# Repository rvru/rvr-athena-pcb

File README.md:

# RVR Athena PCB
**Contributor(s):** Jennifer Hellar 

**Contact(s):** jennifer.hellar@rice.edu

### Revisions
#### Rev. 0.1 (r0p1)
An initial (un-manufactured) design featuring a simplified version of the HiFive
reference design without the WiFi module and a new LiPo battery charger and
connector to enable IoT prototyping.

### Reference Designs
- SiFive HiFive Rev. B
- Sparkfun RED-V RedBoard
- Adafruit Feather M0 Bluefruit LE

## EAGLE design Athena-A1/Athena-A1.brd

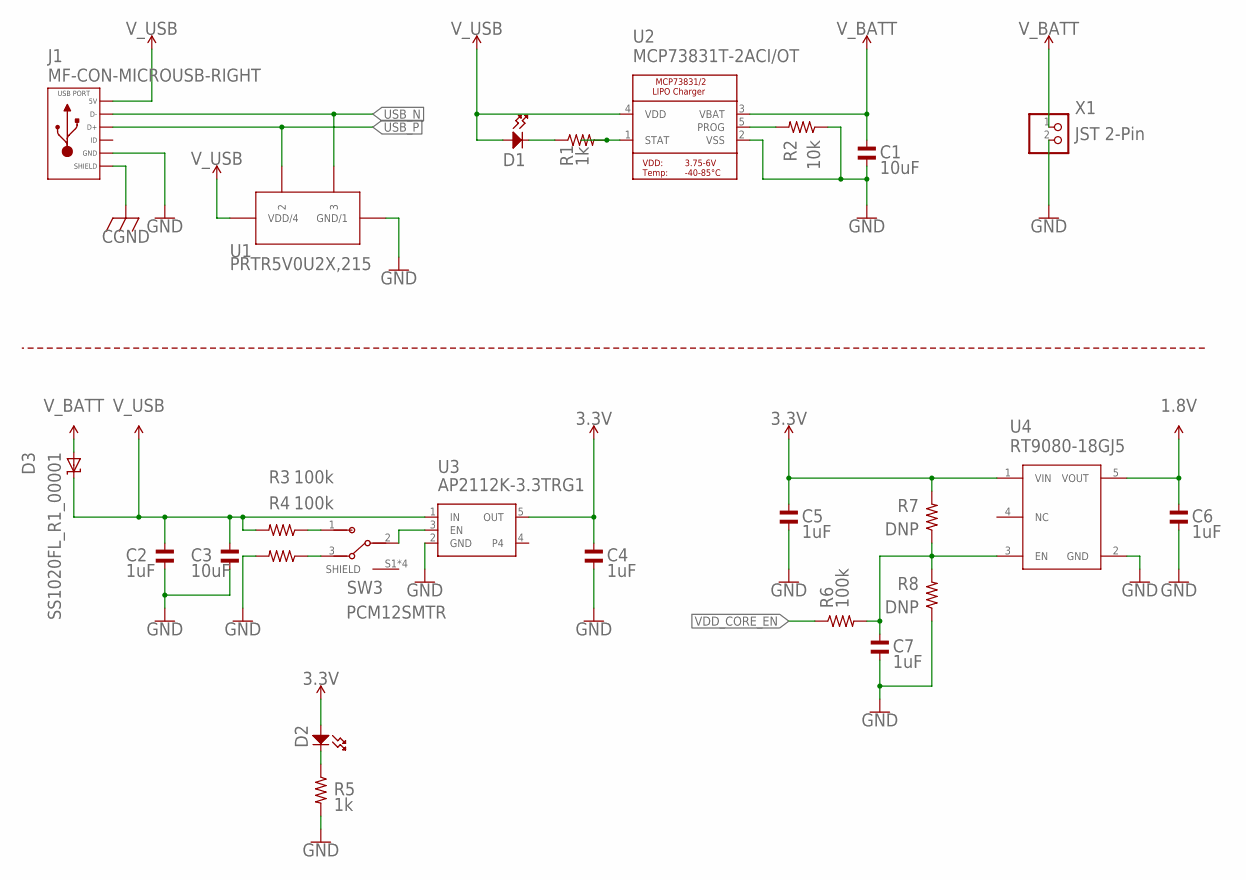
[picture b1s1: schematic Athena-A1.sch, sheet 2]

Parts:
C1, C3: 10uF; C0402; MPN CL05A106MP8NUB8
C2, C4, C5, C6, C7: 1uF; C0402
D1: MF-LED-0805-RED; LED0603
D2: MF-LED-0603-GREEN; LED0603
D3: SS1020FL_R1_00001; SOD-123
J1: MF-CON-MICROUSB-RIGHT; MICROUSB-RIGHT
R1, R5: 1k; R0402
R2: 10k; R0402
R3, R4, R6: 100k; R0402
R7, R8: DNP; R0402
SW3: PCM12SMTR; SW_PCM12SMTR
U1: PRTR5V0U2X,215; SOT143B_PRTR5V0U2X,215_NEX
U2: MCP73831T-2ACI/OT; SOT23-5
U3: AP2112K-3.3TRG1; SOT23-5
U4: RT9080-18GJ5; TSOT23-5_ONS
X1: JST 2-Pin; JSTPH2

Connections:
1.8V: C6.P$1, U4.5 (VOUT); also elsewhere on the board
3.3V: C4.P$1, C5.P$1, D2.ANODE, R7.P$2, U3.5 (OUT), U4.1 (VIN); also elsewhere on the board
CGND: J1.S1 (SLD), J1.S2 (SLD), J1.S3 (SLD), J1.S4 (SLD), J1.S5 (SLD), J1.S6 (SLD); also elsewhere on the board
GND: C1.P$2, C2.P$2, C3.P$2, C4.P$2, C5.P$2, C6.P$2, C7.P$2, J1.5 (GND), R2.P$1, R4.P$2, R5.P$2, R8.P$1, U1.1 (GND/1), U2.2 (VSS), U3.2 (GND), U4.2 (GND), X1.2; also elsewhere on the board
unnamed: R3.P$1, SW3.1
unnamed: D2.CATHODE, R5.P$1
unnamed: D1.CATHODE, R1.P$1
unnamed: C7.P$1, R6.P$2, R7.P$1, R8.P$2, U4.3 (EN)
unnamed: R2.P$2, U2.5 (PROG)
unnamed: R1.P$2, U2.1 (STAT)
unnamed: SW3.2, U3.3 (EN)
unnamed: R4.P$1, SW3.3
USB_N: J1.2 (D-), U1.3; also elsewhere on the board
USB_P: J1.3 (D+), U1.2; also elsewhere on the board
VDD_CORE_EN: R6.P$1; also elsewhere on the board
V_BATT: C1.P$1, D3.A, U2.3 (VBAT), X1.1
V_USB: C2.P$1, C3.P$1, D1.ANODE, D3.C, J1.1 (5V), R3.P$2, U1.4 (VDD/4), U2.4 (VDD), U3.1 (IN); also elsewhere on the board

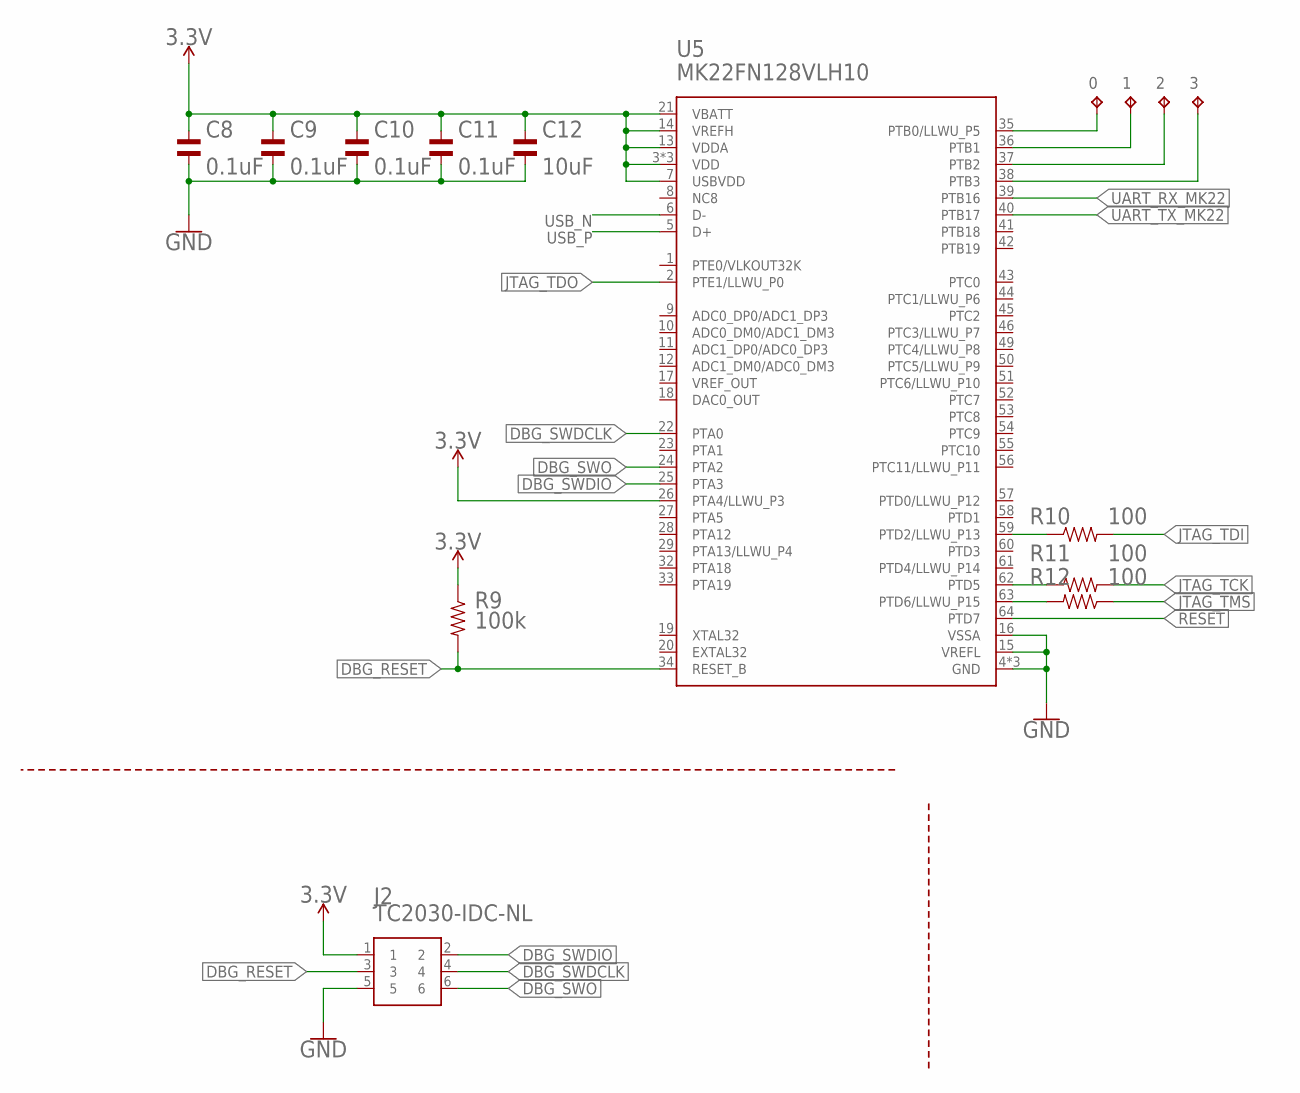
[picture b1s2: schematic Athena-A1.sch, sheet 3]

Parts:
0, 1, 2, 3: TPB0,65; TP_B0,65
C8, C9, C10, C11: 0.1uF; C0402
C12: 10uF; C0402; MPN CL05A106MP8NUB8
J2: TC2030-IDC-NL; TAG_TC2030-IDC-NL
R9: 100k; R0402
R10, R11, R12: 100; R0402
U5: MK22FN128VLH10; IC_USB_JTAG_LQFP-64

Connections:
3.3V: C8.P$1, C9.P$1, C10.P$1, C11.P$1, C12.P$1, J2.1, R9.P$1, U5.3 (VDD), U5.7 (USBVDD), U5.13 (VDDA), U5.14 (VREFH), U5.21 (VBATT), U5.26 (PTA4/LLWU_P3), U5.30 (VDD), U5.48 (VDD); also elsewhere on the board
DBG_RESET: J2.3, R9.P$2, U5.34 (RESET_B)
DBG_SWDCLK: J2.4, U5.22 (PTA0)
DBG_SWDIO: J2.2, U5.25 (PTA3)
DBG_SWO: J2.6, U5.24 (PTA2)
GND: C8.P$2, C9.P$2, C10.P$2, C11.P$2, C12.P$2, J2.5, U5.4 (GND), U5.15 (VREFL), U5.16 (VSSA), U5.31 (GND), U5.47 (GND); also elsewhere on the board
JTAG_TCK: R11.P$2; also elsewhere on the board
JTAG_TDI: R10.P$2; also elsewhere on the board
JTAG_TDO: U5.2 (PTE1/LLWU_P0); also elsewhere on the board
JTAG_TMS: R12.P$1; also elsewhere on the board
unnamed: R12.P$2, U5.63 (PTD6/LLWU_P15)
unnamed: R11.P$1, U5.62 (PTD5)
unnamed: R10.P$1, U5.59 (PTD2/LLWU_P13)
unnamed: 0.TP, U5.35 (PTB0/LLWU_P5)
unnamed: 1.TP, U5.36 (PTB1)
unnamed: 2.TP, U5.37 (PTB2)
unnamed: 3.TP, U5.38 (PTB3)
RESET: U5.64 (PTD7); also elsewhere on the board
UART_RX_MK22: U5.39 (PTB16); also elsewhere on the board
UART_TX_MK22: U5.40 (PTB17); also elsewhere on the board
USB_N: U5.6 (D-); also elsewhere on the board
USB_P: U5.5 (D+); also elsewhere on the board

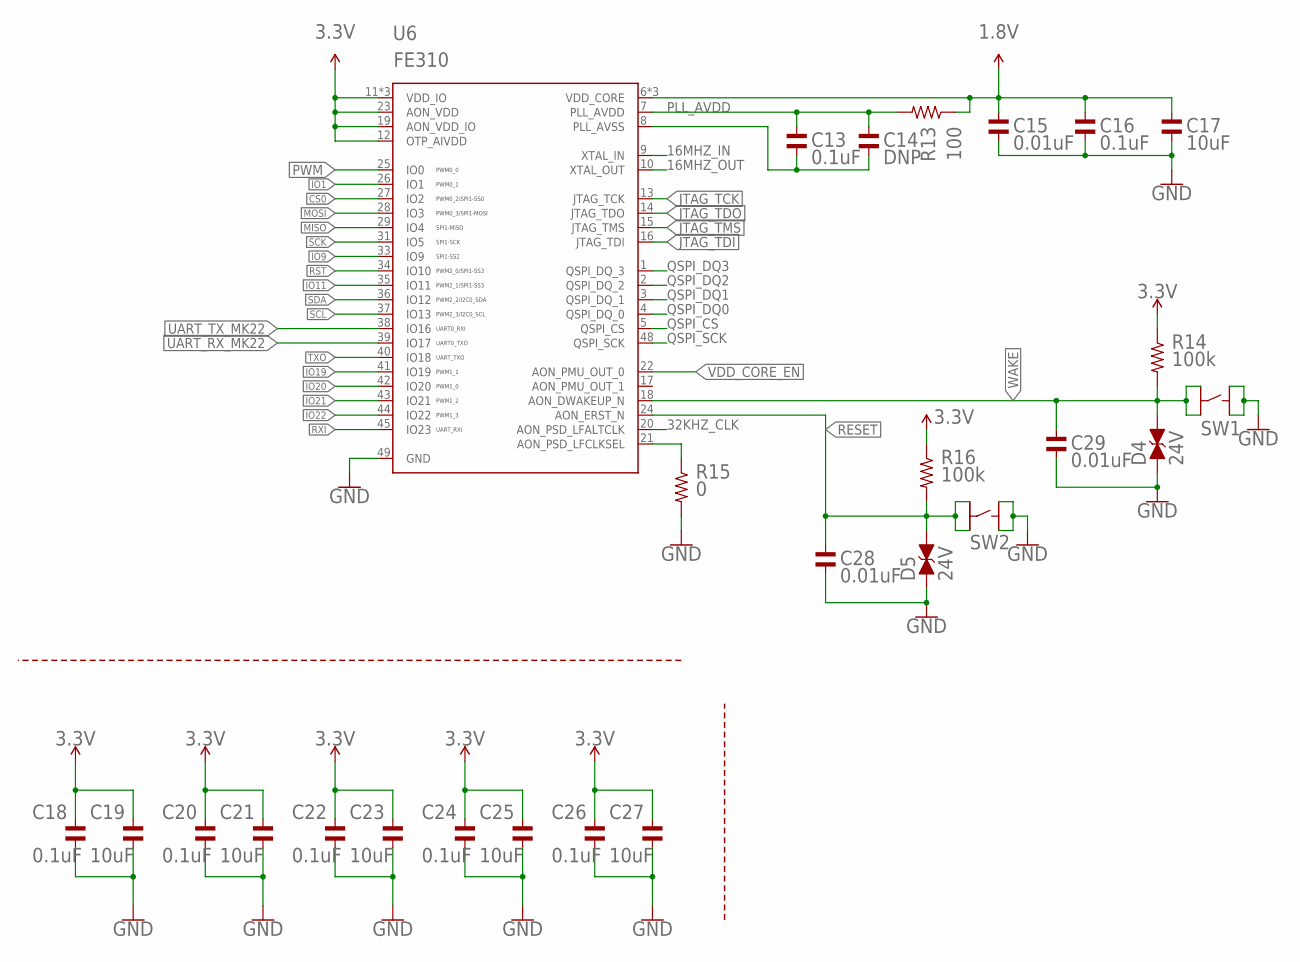
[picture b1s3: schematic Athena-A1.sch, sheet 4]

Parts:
C13, C16, C18, C20, C22, C24, C26: 0.1uF; C0402
C14: DNP; C0402
C15, C28, C29: 0.01uF; C0402
C17, C19, C21, C23, C25, C27: 10uF; C0402; MPN CL05A106MP8NUB8
D4, D5: 24V; TVS0603
R13: 100; R0402
R14, R16: 100k; R0402
R15: 0; R0402
SW1, SW2: MF-SW-TACT-6MM; TACT4.2MM
U6: FE310; MCU_QFN-48-.4MMPITCH

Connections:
1.8V: C15.P$1, C16.P$1, C17.P$1, R13.P$1, U6.6 (VDD_CORE), U6.30 (VDD_CORE), U6.46 (VDD_CORE); also elsewhere on the board
3.3V: C18.P$1, C19.P$1, C20.P$1, C21.P$1, C22.P$1, C23.P$1, C24.P$1, C25.P$1, C26.P$1, C27.P$1, R14.P$1, R16.P$1, U6.11 (VDD_IO), U6.12 (OTP_AIVDD), U6.19 (AON_VDD_IO), U6.23 (AON_VDD), U6.32 (VDD_IO), U6.47 (VDD_IO); also elsewhere on the board
16MHZ_IN: U6.9 (XTAL_IN); also elsewhere on the board
16MHZ_OUT: U6.10 (XTAL_OUT); also elsewhere on the board
32KHZ_CLK: U6.20 (AON_PSD_LFALTCLK); also elsewhere on the board
CS0: U6.27 (IO2); also elsewhere on the board
GND: C15.P$2, C16.P$2, C17.P$2, C18.P$2, C19.P$2, C20.P$2, C21.P$2, C22.P$2, C23.P$2, C24.P$2, C25.P$2, C26.P$2, C27.P$2, C28.P$2, C29.P$2, D4.1 (A), D5.1 (A), R15.P$2, SW1.P$1, SW1.P$2, SW2.P$1, SW2.P$2, U6.49 (GND); also elsewhere on the board
IO1: U6.26 (IO1); also elsewhere on the board
IO9: U6.33 (IO9); also elsewhere on the board
IO11: U6.35 (IO11); also elsewhere on the board
IO19: U6.41 (IO19); also elsewhere on the board
IO20: U6.42 (IO20); also elsewhere on the board
IO21: U6.43 (IO21); also elsewhere on the board
IO22: U6.44 (IO22); also elsewhere on the board
JTAG_TCK: U6.13 (JTAG_TCK); also elsewhere on the board
JTAG_TDI: U6.16 (JTAG_TDI); also elsewhere on the board
JTAG_TDO: U6.14 (JTAG_TDO); also elsewhere on the board
JTAG_TMS: U6.15 (JTAG_TMS); also elsewhere on the board
MISO: U6.29 (IO4); also elsewhere on the board
MOSI: U6.28 (IO3); also elsewhere on the board
unnamed: R15.P$1, U6.21 (AON_PSD_LFCLKSEL)
unnamed: C13.P$2, C14.P$2, U6.8 (PLL_AVSS)
PLL_AVDD: C13.P$1, C14.P$1, R13.P$2, U6.7 (PLL_AVDD)
PWM: U6.25 (IO0); also elsewhere on the board
QSPI_CS: U6.5 (QSPI_CS); also elsewhere on the board
QSPI_DQ0: U6.4 (QSPI_DQ_0); also elsewhere on the board
QSPI_DQ1: U6.3 (QSPI_DQ_1); also elsewhere on the board
QSPI_DQ2: U6.2 (QSPI_DQ_2); also elsewhere on the board
QSPI_DQ3: U6.1 (QSPI_DQ_3); also elsewhere on the board
QSPI_SCK: U6.48 (QSPI_SCK); also elsewhere on the board
RESET: C28.P$1, D5.2 (C), R16.P$2, SW2.P$3, SW2.P$4, U6.24 (AON_ERST_N); also elsewhere on the board
RST: U6.34 (IO10); also elsewhere on the board
RXI: U6.45 (IO23); also elsewhere on the board
SCK: U6.31 (IO5); also elsewhere on the board
SCL: U6.37 (IO13); also elsewhere on the board
SDA: U6.36 (IO12); also elsewhere on the board
TXO: U6.40 (IO18); also elsewhere on the board
UART_RX_MK22: U6.39 (IO17); also elsewhere on the board
UART_TX_MK22: U6.38 (IO16); also elsewhere on the board
VDD_CORE_EN: U6.22 (AON_PMU_OUT_0); also elsewhere on the board
WAKE: C29.P$1, D4.2 (C), R14.P$2, SW1.P$3, SW1.P$4, U6.18 (AON_DWAKEUP_N)

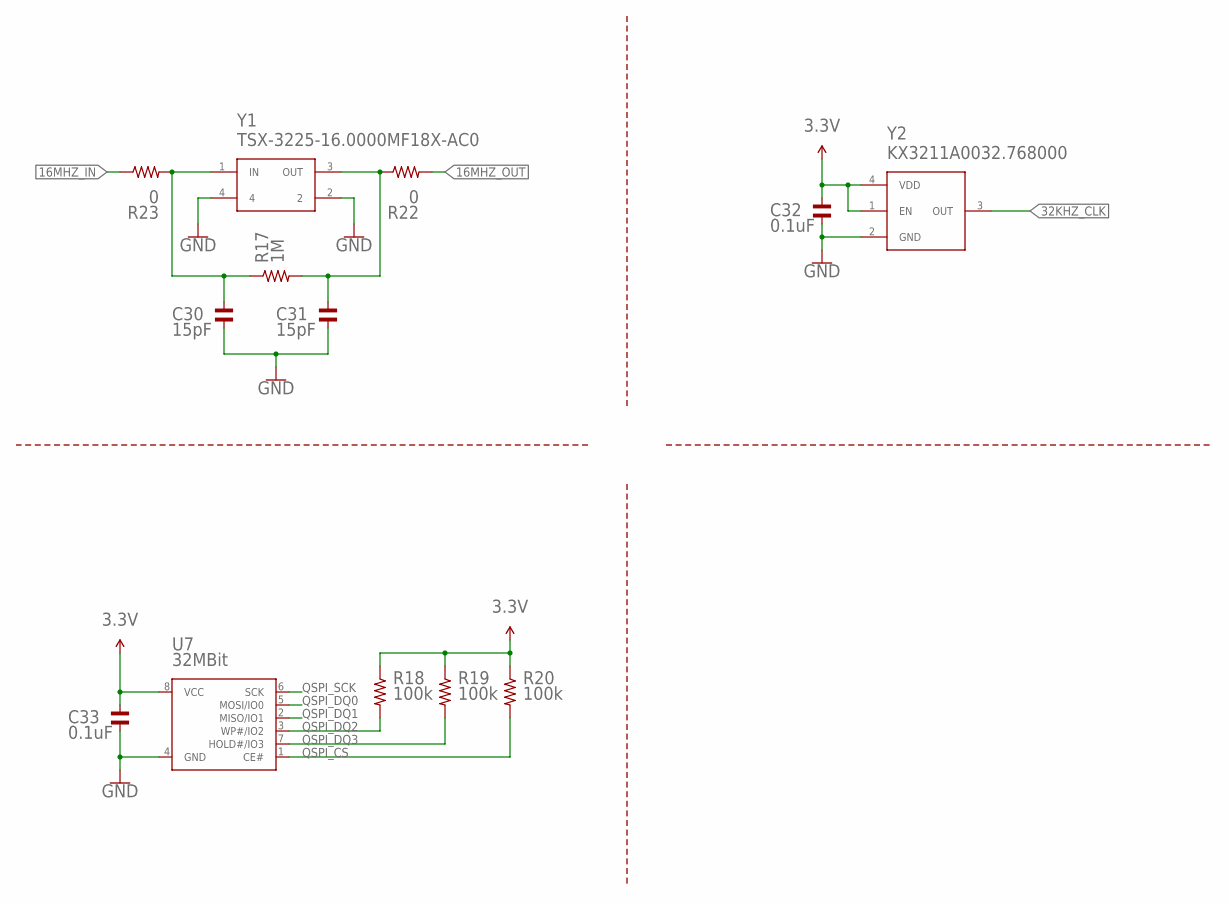
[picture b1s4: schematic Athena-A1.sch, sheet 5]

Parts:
C30, C31: 15pF; C0402; MPN CL05C150JB5NNNC
C32, C33: 0.1uF; C0402
R17: 1M; R0402
R18, R19, R20: 100k; R0402
R22, R23: 0; R0402
U7: 32MBit; IC-MEMORY_SO08
Y1: TSX-3225-16.0000MF18X-AC0; SMD-4
Y2: KX3211A0032.768000; SMD-4

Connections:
3.3V: C32.P$1, C33.P$1, R18.P$1, R19.P$1, R20.P$1, U7.8 (VCC), Y2.1 (EN), Y2.4 (VDD); also elsewhere on the board
16MHZ_IN: R23.P$1; also elsewhere on the board
16MHZ_OUT: R22.P$2; also elsewhere on the board
32KHZ_CLK: Y2.3 (OUT); also elsewhere on the board
GND: C30.P$2, C31.P$2, C32.P$2, C33.P$2, U7.4 (GND), Y1.2, Y1.4, Y2.2 (GND); also elsewhere on the board
unnamed: C30.P$1, R17.P$1, R23.P$2, Y1.1 (IN)
unnamed: C31.P$1, R17.P$2, R22.P$1, Y1.3 (OUT)
QSPI_CS: R20.P$2, U7.1 (CE#); also elsewhere on the board
QSPI_DQ0: U7.5 (MOSI/IO0); also elsewhere on the board
QSPI_DQ1: U7.2 (MISO/IO1); also elsewhere on the board
QSPI_DQ2: R18.P$2, U7.3 (WP#/IO2); also elsewhere on the board
QSPI_DQ3: R19.P$2, U7.7 (HOLD#/IO3); also elsewhere on the board
QSPI_SCK: U7.6 (SCK); also elsewhere on the board

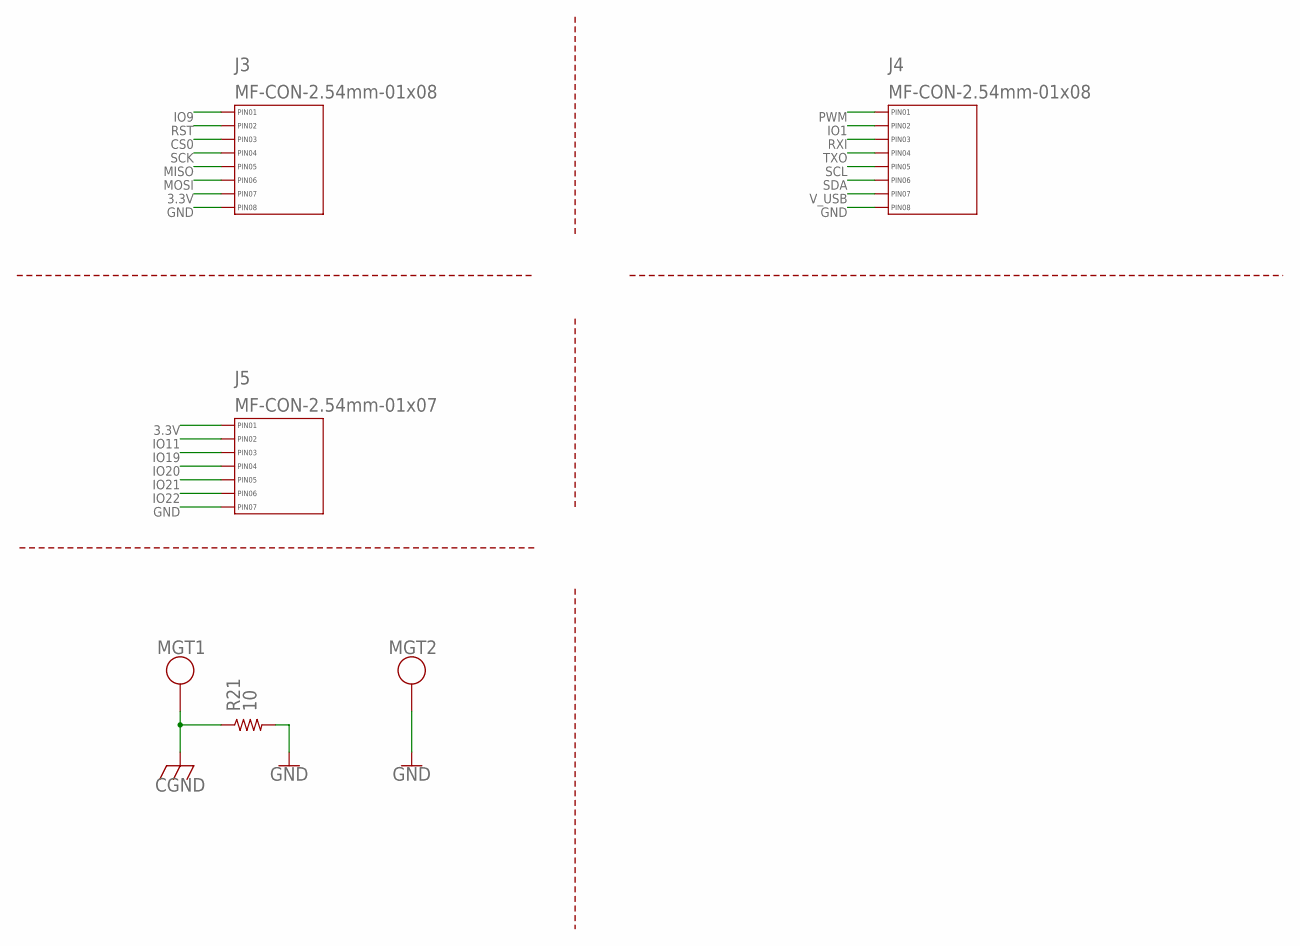
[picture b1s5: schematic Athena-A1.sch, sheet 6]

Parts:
J3, J4: MF-CON-2.54mm-01x08; PTH_2.54MM_01X08
J5: MF-CON-2.54mm-01x07; PTH_2.54MM_01X07
MGT1, MGT2: MOUNTING_HOLE
R21: 10; R0402

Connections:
3.3V: J3.P$7 (PIN7), J5.P$1 (PIN1); also elsewhere on the board
CGND: MGT1.P$1, R21.P$1; also elsewhere on the board
CS0: J3.P$3 (PIN3); also elsewhere on the board
GND: J3.P$8 (PIN8), J4.P$8 (PIN8), J5.P$7 (PIN7), MGT2.P$1, R21.P$2; also elsewhere on the board
IO1: J4.P$2 (PIN2); also elsewhere on the board
IO9: J3.P$1 (PIN1); also elsewhere on the board
IO11: J5.P$2 (PIN2); also elsewhere on the board
IO19: J5.P$3 (PIN3); also elsewhere on the board
IO20: J5.P$4 (PIN4); also elsewhere on the board
IO21: J5.P$5 (PIN5); also elsewhere on the board
IO22: J5.P$6 (PIN6); also elsewhere on the board
MISO: J3.P$5 (PIN5); also elsewhere on the board
MOSI: J3.P$6 (PIN6); also elsewhere on the board
PWM: J4.P$1 (PIN1); also elsewhere on the board
RST: J3.P$2 (PIN2); also elsewhere on the board
RXI: J4.P$3 (PIN3); also elsewhere on the board
SCK: J3.P$4 (PIN4); also elsewhere on the board
SCL: J4.P$5 (PIN5); also elsewhere on the board
SDA: J4.P$6 (PIN6); also elsewhere on the board
TXO: J4.P$4 (PIN4); also elsewhere on the board
V_USB: J4.P$7 (PIN7); also elsewhere on the board

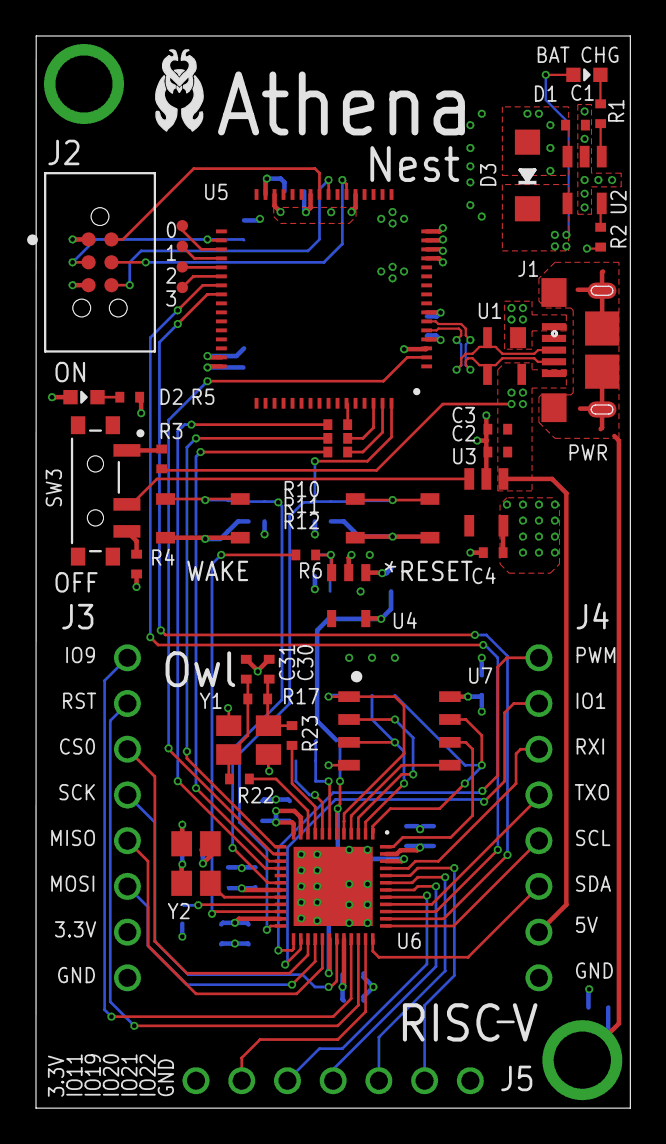
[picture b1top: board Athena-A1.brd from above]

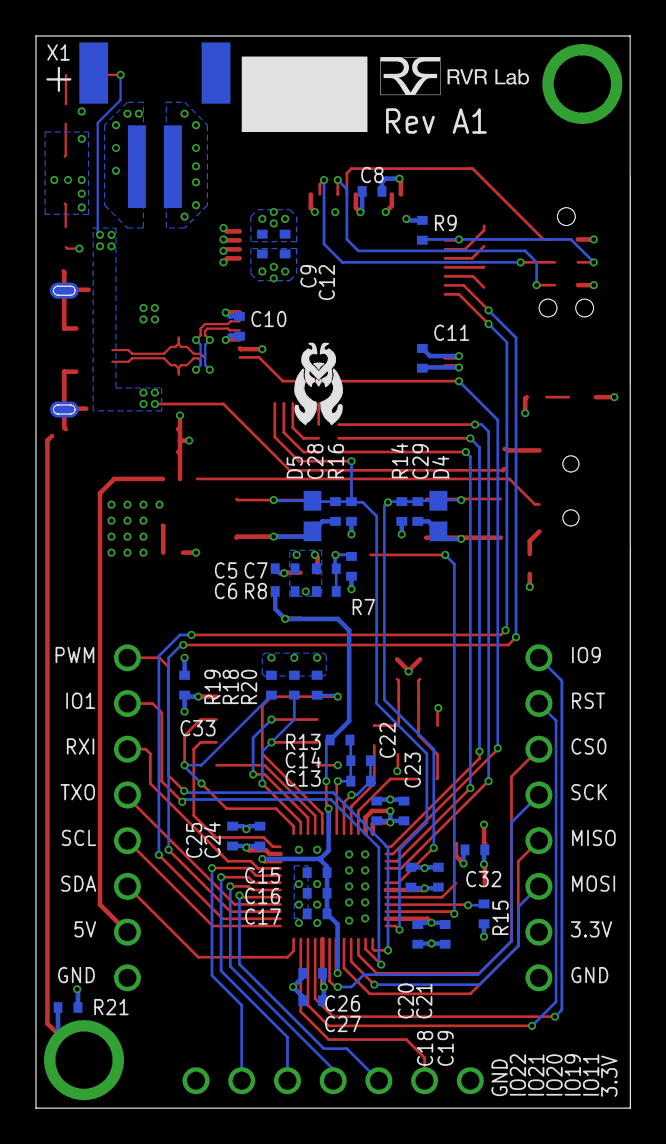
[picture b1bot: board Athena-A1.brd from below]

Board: 4 copper layers, 33.0 x 59.6 mm, 85 parts (41 on the bottom side), 67 nets.

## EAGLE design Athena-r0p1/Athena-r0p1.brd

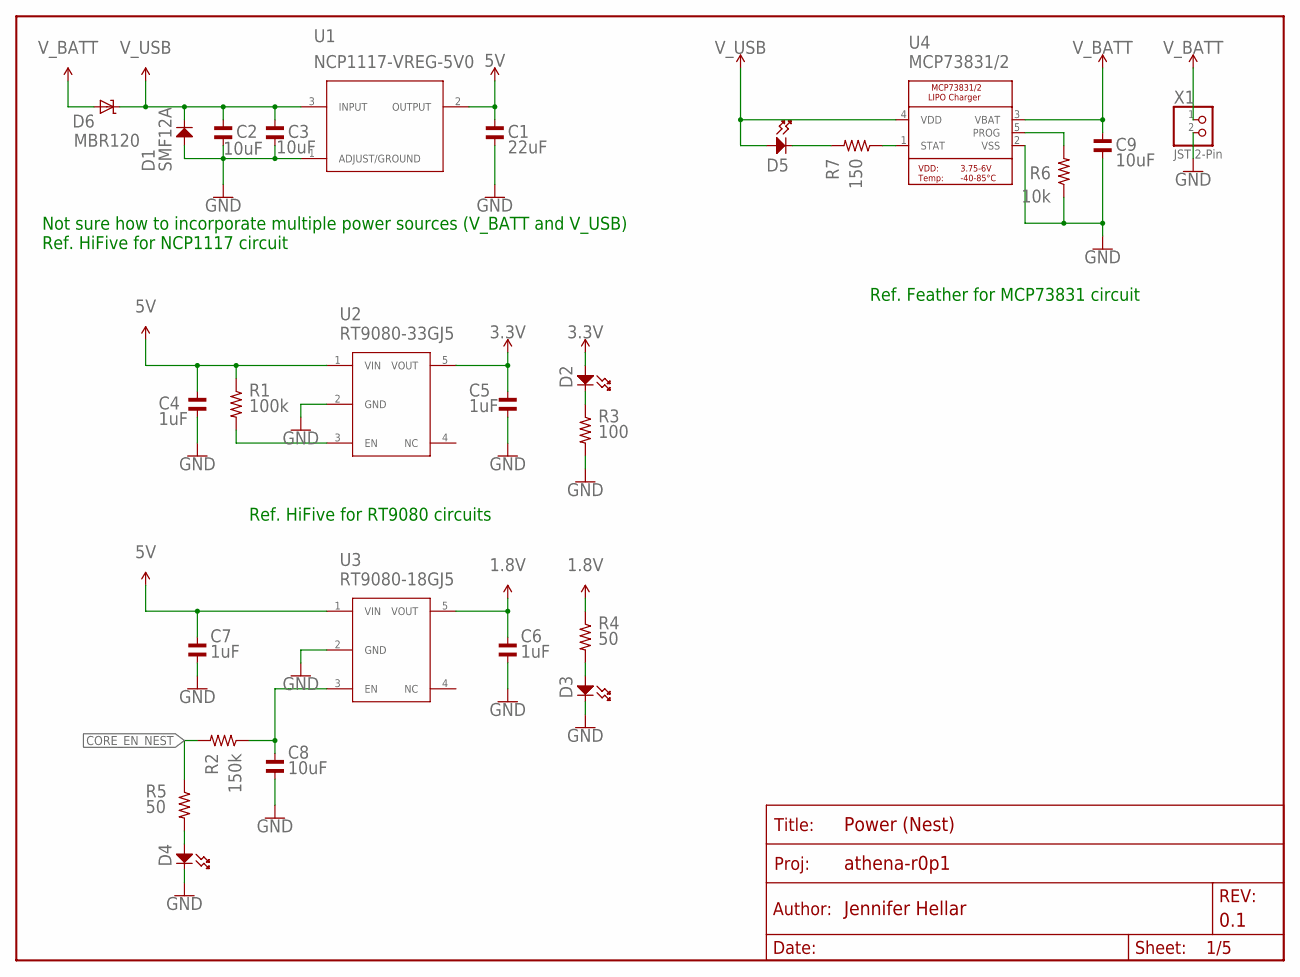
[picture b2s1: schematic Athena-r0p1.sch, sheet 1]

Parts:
C1: 22uF; C0603
C2, C3, C8, C9: 10uF; C0603
C4, C5, C6, C7: 1uF; C0603
D1: SMF12A; SMFSERIES_LTF
D2, D3, D4: MF-LED-0603-GREEN; LED0603
D5: MF-LED-0603-RED; LED0603
D6: MBR120; SOD-123
FRAME1: FRAME-LETTER; SPARKFUN-AESTHETICS_CREATIVE_COMMONS
R1: 100k; R0603
R2: 150k; R0603
R3: 100; R0603
R4, R5: 50; R0603
R6: 10k; R0603
R7: 150; R0603
U1: NCP1117-VREG-5V0; SOT223-3_ONS
U2: RT9080-33GJ5; TSOT23-5_ONS
U3: RT9080-18GJ5; TSOT23-5_ONS
U4: MCP73831/2; SOT23-5
X1: JST 2-Pin; JSTPH2

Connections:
1.8V: C6.P$1, R4.P$1, U3.5 (VOUT); also elsewhere on the board
3.3V: C5.P$1, D2.ANODE, U2.5 (VOUT); also elsewhere on the board
5V: C1.P$1, C4.P$1, C7.P$1, R1.P$1, U1.2 (OUTPUT), U2.1 (VIN), U3.1 (VIN); also elsewhere on the board
CORE_EN_NEST: R2.P$2, R5.P$1; also elsewhere on the board
GND: C1.P$2, C2.P$2, C3.P$2, C4.P$2, C5.P$2, C6.P$2, C7.P$2, C8.P$2, C9.P$2, D1.2 (ANODE), D3.CATHODE, D4.CATHODE, R3.P$2, R6.P$1, U1.1 (ADJUST/GROUND), U2.2 (GND), U3.2 (GND), U4.2 (VSS), X1.2; also elsewhere on the board
unnamed: D3.ANODE, R4.P$2
unnamed: D2.CATHODE, R3.P$1
unnamed: R1.P$2, U2.3 (EN)
unnamed: C8.P$1, R2.P$1, U3.3 (EN)
unnamed: D4.ANODE, R5.P$2
unnamed: R7.P$1, U4.1 (STAT)
unnamed: R6.P$2, U4.5 (PROG)
unnamed: D5.CATHODE, R7.P$2
V_BATT: C9.P$1, D6.A, U4.3 (VBAT), X1.1
V_USB: C2.P$1, C3.P$1, D1.1 (CATHODE), D5.ANODE, D6.C, U1.3 (INPUT), U4.4 (VDD); also elsewhere on the board

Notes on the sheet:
Not sure how to incorporate multiple power sources (V_BATT and V_USB) Ref. HiFive for NCP1117 circuit
Ref. HiFive for RT9080 circuits
Ref. Feather for MCP73831 circuit

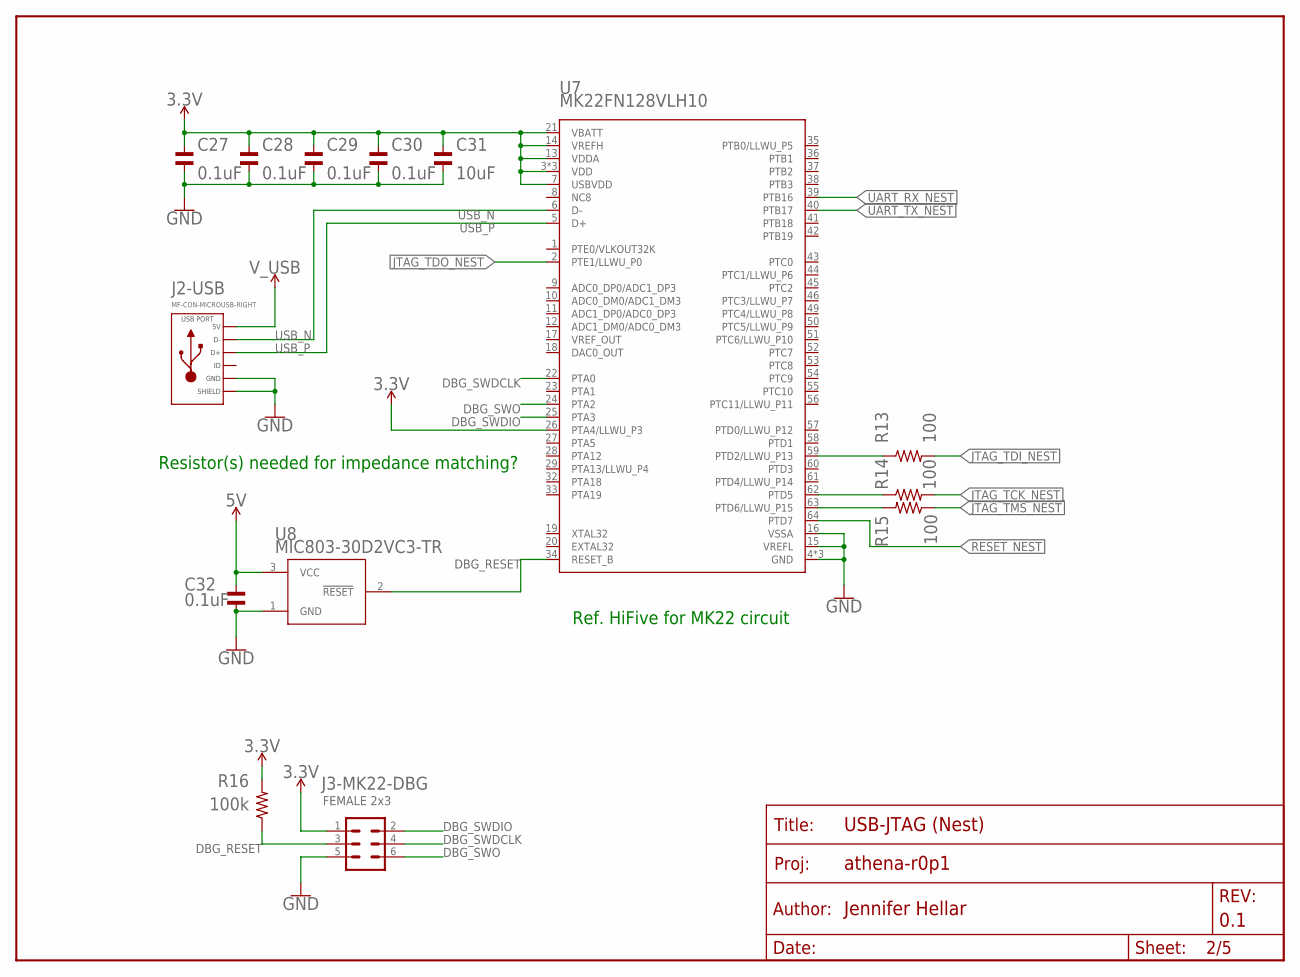
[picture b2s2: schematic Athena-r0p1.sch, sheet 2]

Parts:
C27, C28, C29, C30, C32: 0.1uF; C0603
C31: 10uF; C0603
FRAME3: FRAME-LETTER; SPARKFUN-AESTHETICS_CREATIVE_COMMONS
J2-USB: MF-CON-MICROUSB-RIGHT; MICROUSB-RIGHT
J3-MK22-DBG: FEMALE 2x3; 2X3
R13, R14, R15: 100; R0603
R16: 100k; R0603
U7: MK22FN128VLH10; IC_USB_JTAG_LQFP-64
U8: MIC803-30D2VC3-TR; SC-70_C3_MCH

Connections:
3.3V: C27.P$1, C28.P$1, C29.P$1, C30.P$1, C31.P$1, J3-MK22-DBG.1, R16.P$2, U7.3 (VDD), U7.7 (USBVDD), U7.13 (VDDA), U7.14 (VREFH), U7.21 (VBATT), U7.26 (PTA4/LLWU_P3), U7.30 (VDD), U7.48 (VDD); also elsewhere on the board
5V: C32.P$1, U8.3 (VCC); also elsewhere on the board
DBG_RESET: J3-MK22-DBG.3, R16.P$1, U7.34 (RESET_B), U8.2 (!RESET)
DBG_SWDCLK: J3-MK22-DBG.4, U7.22 (PTA0)
DBG_SWDIO: J3-MK22-DBG.2, U7.25 (PTA3)
DBG_SWO: J3-MK22-DBG.6, U7.24 (PTA2)
GND: C27.P$2, C28.P$2, C29.P$2, C30.P$2, C31.P$2, C32.P$2, J2-USB.5 (GND), J2-USB.S1 (SLD), J2-USB.S2 (SLD), J2-USB.S3 (SLD), J2-USB.S4 (SLD), J2-USB.S5 (SLD), J2-USB.S6 (SLD), J3-MK22-DBG.5, U7.4 (GND), U7.15 (VREFL), U7.16 (VSSA), U7.31 (GND), U7.47 (GND), U8.1 (GND); also elsewhere on the board
JTAG_TCK_NEST: R14.P$2; also elsewhere on the board
JTAG_TDI_NEST: R13.P$2; also elsewhere on the board
JTAG_TDO_NEST: U7.2 (PTE1/LLWU_P0); also elsewhere on the board
JTAG_TMS_NEST: R15.P$1; also elsewhere on the board
unnamed: R13.P$1, U7.59 (PTD2/LLWU_P13)
unnamed: R14.P$1, U7.62 (PTD5)
unnamed: R15.P$2, U7.63 (PTD6/LLWU_P15)
RESET_NEST: U7.64 (PTD7); also elsewhere on the board
UART_RX_NEST: U7.39 (PTB16); also elsewhere on the board
UART_TX_NEST: U7.40 (PTB17); also elsewhere on the board
USB_N: J2-USB.2 (D-), U7.6 (D-)
USB_P: J2-USB.3 (D+), U7.5 (D+)
V_USB: J2-USB.1 (5V); also elsewhere on the board

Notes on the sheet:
Resistor(s) needed for impedance matching?
Ref. HiFive for MK22 circuit

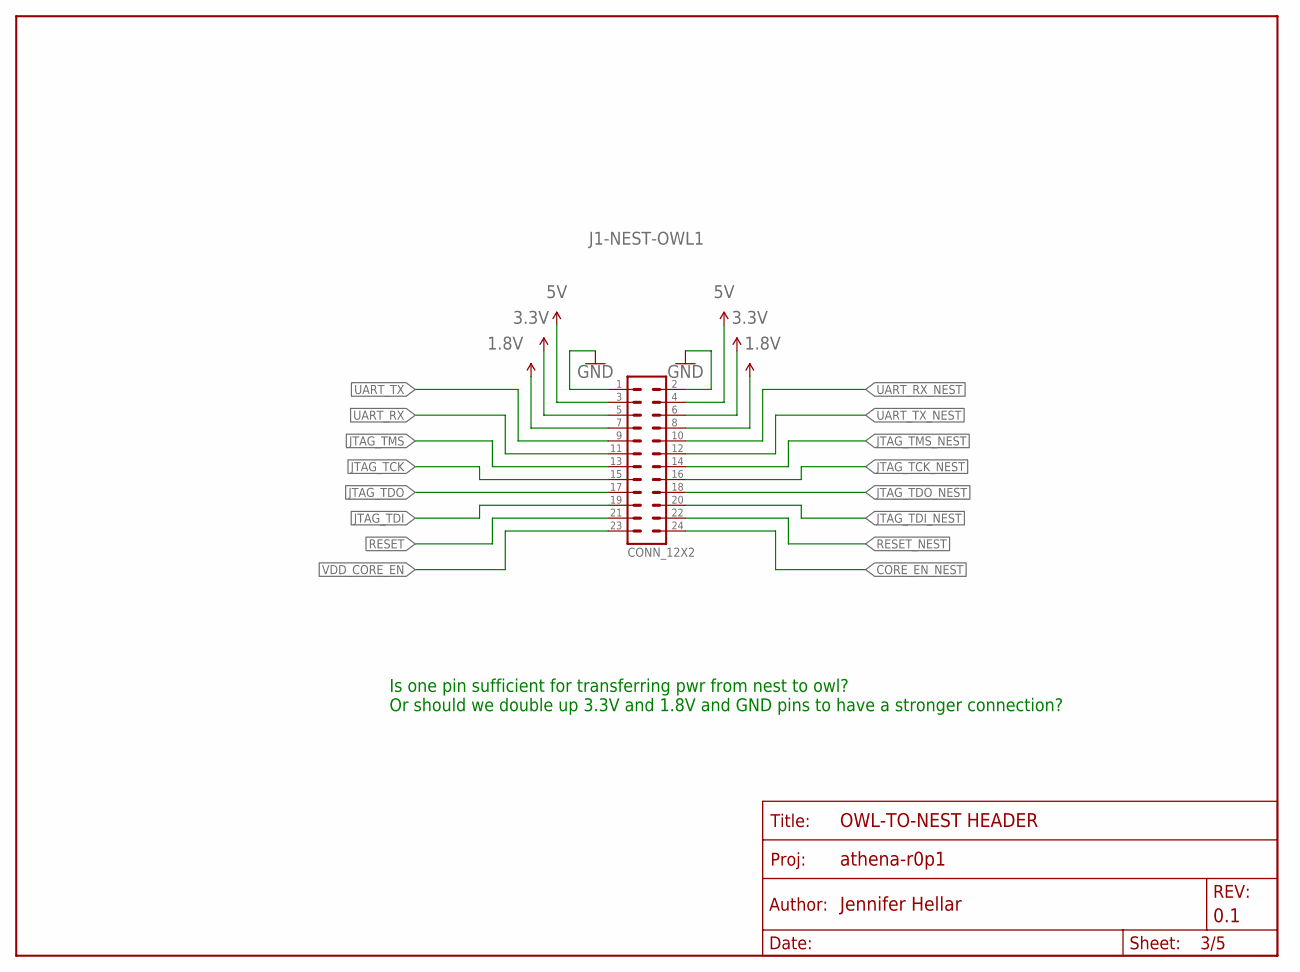
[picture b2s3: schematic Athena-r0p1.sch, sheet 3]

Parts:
FRAME5: FRAME-LETTER; SPARKFUN-AESTHETICS_CREATIVE_COMMONS
J1-NEST-OWL1: CONN_12X2; 2X12

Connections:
1.8V: J1-NEST-OWL1.7, J1-NEST-OWL1.8; also elsewhere on the board
3.3V: J1-NEST-OWL1.5, J1-NEST-OWL1.6; also elsewhere on the board
5V: J1-NEST-OWL1.3, J1-NEST-OWL1.4; also elsewhere on the board
CORE_EN_NEST: J1-NEST-OWL1.24; also elsewhere on the board
GND: J1-NEST-OWL1.1, J1-NEST-OWL1.2; also elsewhere on the board
JTAG_TCK: J1-NEST-OWL1.15; also elsewhere on the board
JTAG_TCK_NEST: J1-NEST-OWL1.16; also elsewhere on the board
JTAG_TDI: J1-NEST-OWL1.19; also elsewhere on the board
JTAG_TDI_NEST: J1-NEST-OWL1.20; also elsewhere on the board
JTAG_TDO: J1-NEST-OWL1.17; also elsewhere on the board
JTAG_TDO_NEST: J1-NEST-OWL1.18; also elsewhere on the board
JTAG_TMS: J1-NEST-OWL1.13; also elsewhere on the board
JTAG_TMS_NEST: J1-NEST-OWL1.14; also elsewhere on the board
RESET: J1-NEST-OWL1.21; also elsewhere on the board
RESET_NEST: J1-NEST-OWL1.22; also elsewhere on the board
UART_RX: J1-NEST-OWL1.11; also elsewhere on the board
UART_RX_NEST: J1-NEST-OWL1.10; also elsewhere on the board
UART_TX: J1-NEST-OWL1.9; also elsewhere on the board
UART_TX_NEST: J1-NEST-OWL1.12; also elsewhere on the board
VDD_CORE_EN: J1-NEST-OWL1.23; also elsewhere on the board

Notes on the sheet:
Is one pin sufficient for transferring pwr from nest to owl? Or should we double up 3.3V and 1.8V and GND pins to have a stronger connection?

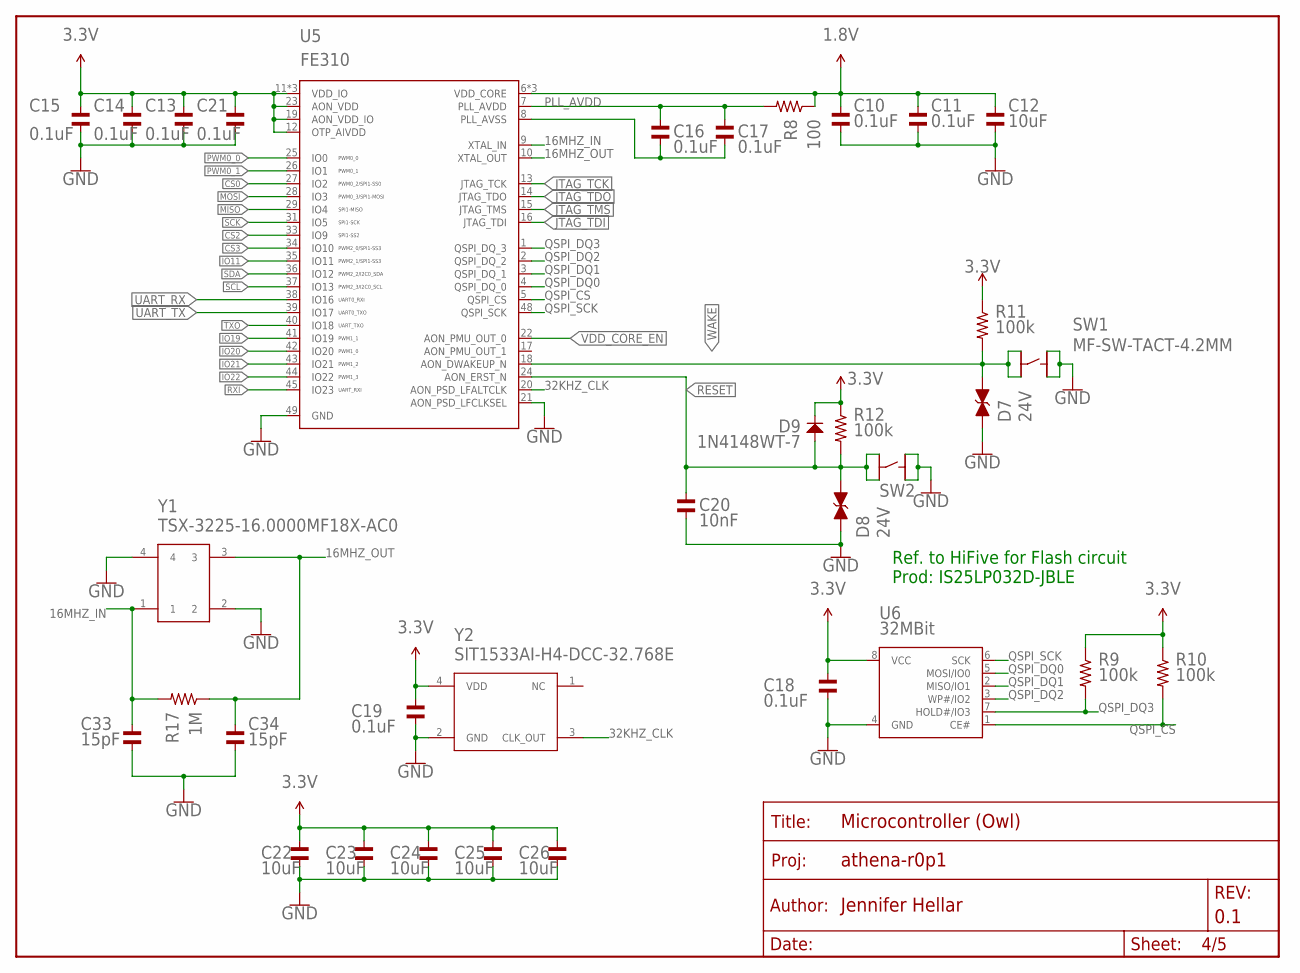
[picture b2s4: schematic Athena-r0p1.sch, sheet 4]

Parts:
C10, C11, C13, C14, C15, C16, C17, C18, C19, C21: 0.1uF; C0603
C12, C22, C23, C24, C25, C26: 10uF; C0603
C20: 10nF; C0603
C33, C34: 15pF; C0603
D7, D8: 24V; SPARKFUN-DISCRETESEMI_0603
D9: 1N4148WT-7; SOD-523
FRAME2: FRAME-LETTER; SPARKFUN-AESTHETICS_CREATIVE_COMMONS
R8: 100; R0603
R9, R10, R11, R12: 100k; R0603
R17: 1M; R0603
SW1, SW2: MF-SW-TACT-4.2MM; TACT4.2MM
U5: FE310; MCU_QFN-48-.4MMPITCH
U6: 32MBit; IC-MEMORY_SO08
Y1: TSX-3225-16.0000MF18X-AC0; TSX-3225
Y2: SIT1533AI-H4-DCC-32.768E; XTAL4_SIT1533_SIT

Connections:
1.8V: C10.P$1, C11.P$1, C12.P$1, R8.P$1, U5.6 (VDD_CORE), U5.30 (VDD_CORE), U5.46 (VDD_CORE); also elsewhere on the board
3.3V: C13.P$1, C14.P$1, C15.P$1, C18.P$1, C19.P$1, C21.P$1, C22.P$1, C23.P$1, C24.P$1, C25.P$1, C26.P$1, D9.K (CATHODE), R9.P$1, R10.P$1, R11.P$1, R12.P$1, U5.11 (VDD_IO), U5.12 (OTP_AIVDD), U5.19 (AON_VDD_IO), U5.23 (AON_VDD), U5.32 (VDD_IO), U5.47 (VDD_IO), U6.8 (VCC), Y2.4 (VDD); also elsewhere on the board
16MHZ_IN: C33.P$1, R17.P$2, U5.9 (XTAL_IN), Y1.1
16MHZ_OUT: C34.P$1, R17.P$1, U5.10 (XTAL_OUT), Y1.3
32KHZ_CLK: U5.20 (AON_PSD_LFALTCLK), Y2.3 (CLK_OUT)
CS0: U5.27 (IO2); also elsewhere on the board
CS2: U5.33 (IO9); also elsewhere on the board
CS3: U5.34 (IO10); also elsewhere on the board
GND: C10.P$2, C11.P$2, C12.P$2, C13.P$2, C14.P$2, C15.P$2, C18.P$2, C19.P$2, C20.P$2, C21.P$2, C22.P$2, C23.P$2, C24.P$2, C25.P$2, C26.P$2, C33.P$2, C34.P$2, D7.1 (A), D8.1 (A), SW1.P$1, SW1.P$2, SW2.P$1, SW2.P$2, U5.21 (AON_PSD_LFCLKSEL), U5.49 (GND), U6.4 (GND), Y1.2, Y1.4, Y2.2 (GND); also elsewhere on the board
IO11: U5.35 (IO11); also elsewhere on the board
IO19: U5.41 (IO19); also elsewhere on the board
IO20: U5.42 (IO20); also elsewhere on the board
IO21: U5.43 (IO21); also elsewhere on the board
IO22: U5.44 (IO22); also elsewhere on the board
JTAG_TCK: U5.13 (JTAG_TCK); also elsewhere on the board
JTAG_TDI: U5.16 (JTAG_TDI); also elsewhere on the board
JTAG_TDO: U5.14 (JTAG_TDO); also elsewhere on the board
JTAG_TMS: U5.15 (JTAG_TMS); also elsewhere on the board
MISO: U5.29 (IO4); also elsewhere on the board
MOSI: U5.28 (IO3); also elsewhere on the board
unnamed: C16.P$2, C17.P$2, U5.8 (PLL_AVSS)
PLL_AVDD: C16.P$1, C17.P$1, R8.P$2, U5.7 (PLL_AVDD)
PWM0_0: U5.25 (IO0); also elsewhere on the board
PWM0_1: U5.26 (IO1); also elsewhere on the board
QSPI_CS: R10.P$2, U5.5 (QSPI_CS), U6.1 (CE#)
QSPI_DQ0: U5.4 (QSPI_DQ_0), U6.5 (MOSI/IO0)
QSPI_DQ1: U5.3 (QSPI_DQ_1), U6.2 (MISO/IO1)
QSPI_DQ2: U5.2 (QSPI_DQ_2), U6.3 (WP#/IO2)
QSPI_DQ3: R9.P$2, U5.1 (QSPI_DQ_3), U6.7 (HOLD#/IO3)
QSPI_SCK: U5.48 (QSPI_SCK), U6.6 (SCK)
RESET: C20.P$1, D8.2 (C), D9.A (ANODE), R12.P$2, SW2.P$3, SW2.P$4, U5.24 (AON_ERST_N); also elsewhere on the board
RXI: U5.45 (IO23); also elsewhere on the board
SCK: U5.31 (IO5); also elsewhere on the board
SCL: U5.37 (IO13); also elsewhere on the board
SDA: U5.36 (IO12); also elsewhere on the board
TXO: U5.40 (IO18); also elsewhere on the board
UART_RX: U5.38 (IO16); also elsewhere on the board
UART_TX: U5.39 (IO17); also elsewhere on the board
VDD_CORE_EN: U5.22 (AON_PMU_OUT_0); also elsewhere on the board
WAKE: D7.2 (C), R11.P$2, SW1.P$3, SW1.P$4, U5.18 (AON_DWAKEUP_N); also elsewhere on the board

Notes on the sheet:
Ref. to HiFive for Flash circuit Prod: IS25LP032D-JBLE

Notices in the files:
Athena-A1/Athena-A1.sch:
Copyright © 2022 Rice University
parts and their libraries:
COPYRIGHT: Copyright (C) 2021 Ultra Librarian. All rights reserved.
SparkFun-Connectors: Licensing: Creative Commons ShareAlike 4.0 International - https://creativecommons.org/licenses/by-sa/4.0
COPYRIGHT: Copyright (C) 2016 Accelerated Designs. All rights reserved
